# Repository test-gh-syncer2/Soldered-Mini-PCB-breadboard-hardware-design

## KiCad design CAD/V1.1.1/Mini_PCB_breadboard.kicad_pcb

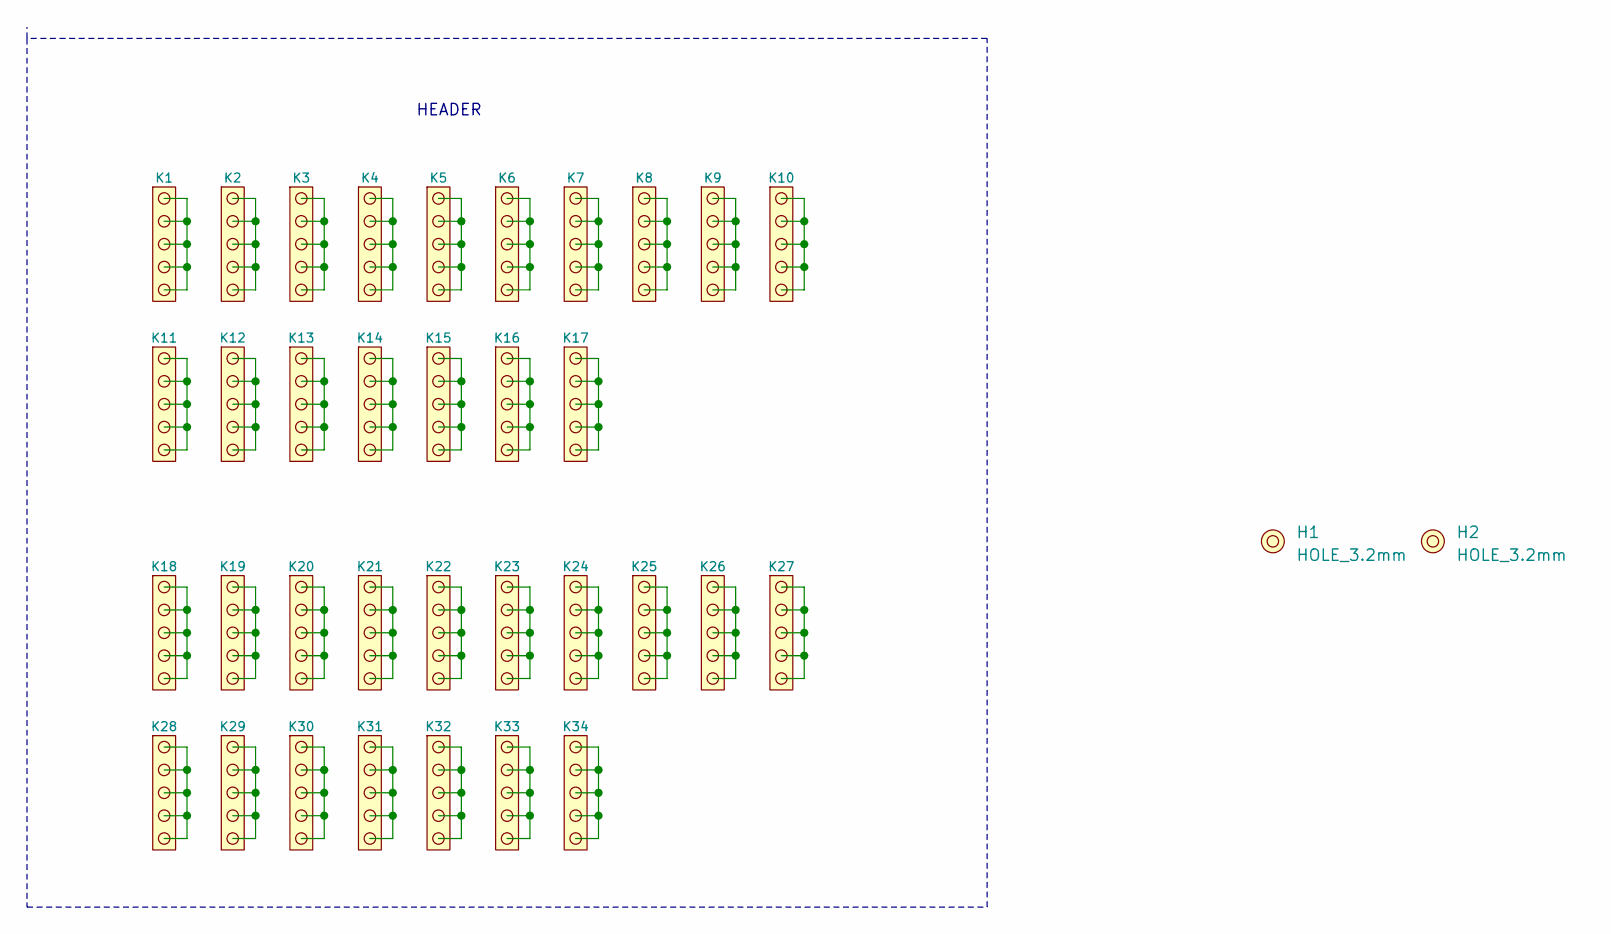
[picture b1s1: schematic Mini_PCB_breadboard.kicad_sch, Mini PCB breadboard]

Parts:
H1, H2: HOLE_3.2mm
K1, K2, K3, K4, K5, K6, K7, K8, K9, K10, K11, K12, K13, K14, K15, K16, K17, K18, K19, K20, K21, K22, K23, K24, K25, K26, K27, K28, K29, K30, K31, K32, K33, K34: HEADER_MALE_5X1

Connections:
unnamed: K1.1, K1.2, K1.3, K1.4, K1.5
unnamed: K2.1, K2.2, K2.3, K2.4, K2.5
unnamed: K3.1, K3.2, K3.3, K3.4, K3.5
unnamed: K4.1, K4.2, K4.3, K4.4, K4.5
unnamed: K5.1, K5.2, K5.3, K5.4, K5.5
unnamed: K6.1, K6.2, K6.3, K6.4, K6.5
unnamed: K7.1, K7.2, K7.3, K7.4, K7.5
unnamed: K8.1, K8.2, K8.3, K8.4, K8.5
unnamed: K9.1, K9.2, K9.3, K9.4, K9.5
unnamed: K10.1, K10.2, K10.3, K10.4, K10.5
unnamed: K11.1, K11.2, K11.3, K11.4, K11.5
unnamed: K12.1, K12.2, K12.3, K12.4, K12.5
unnamed: K13.1, K13.2, K13.3, K13.4, K13.5
unnamed: K14.1, K14.2, K14.3, K14.4, K14.5
unnamed: K15.1, K15.2, K15.3, K15.4, K15.5
unnamed: K16.1, K16.2, K16.3, K16.4, K16.5
unnamed: K17.1, K17.2, K17.3, K17.4, K17.5
unnamed: K18.1, K18.2, K18.3, K18.4, K18.5
unnamed: K19.1, K19.2, K19.3, K19.4, K19.5
unnamed: K20.1, K20.2, K20.3, K20.4, K20.5
unnamed: K21.1, K21.2, K21.3, K21.4, K21.5
unnamed: K22.1, K22.2, K22.3, K22.4, K22.5
unnamed: K23.1, K23.2, K23.3, K23.4, K23.5
unnamed: K24.1, K24.2, K24.3, K24.4, K24.5
unnamed: K25.1, K25.2, K25.3, K25.4, K25.5
unnamed: K26.1, K26.2, K26.3, K26.4, K26.5
unnamed: K27.1, K27.2, K27.3, K27.4, K27.5
unnamed: K28.1, K28.2, K28.3, K28.4, K28.5
unnamed: K29.1, K29.2, K29.3, K29.4, K29.5
unnamed: K30.1, K30.2, K30.3, K30.4, K30.5
unnamed: K31.1, K31.2, K31.3, K31.4, K31.5
unnamed: K32.1, K32.2, K32.3, K32.4, K32.5
unnamed: K33.1, K33.2, K33.3, K33.4, K33.5
unnamed: K34.1, K34.2, K34.3, K34.4, K34.5

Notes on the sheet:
HEADER

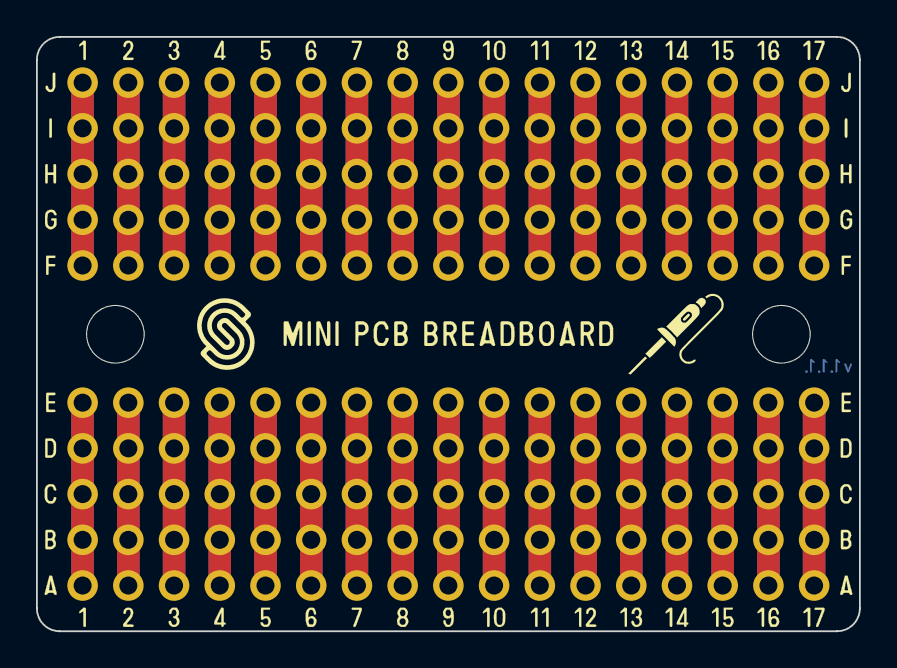
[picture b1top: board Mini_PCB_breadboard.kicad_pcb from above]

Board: 2 copper layers, 45.7 x 33.0 mm, 36 parts (0 on the bottom side), 34 nets.

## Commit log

2021-09-23 Syncing to git
2021-09-23 Updating open source files.
